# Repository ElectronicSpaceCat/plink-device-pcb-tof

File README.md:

# plink-device-pcb-tof
PCB for the Time of Flight (ToF) Sensors

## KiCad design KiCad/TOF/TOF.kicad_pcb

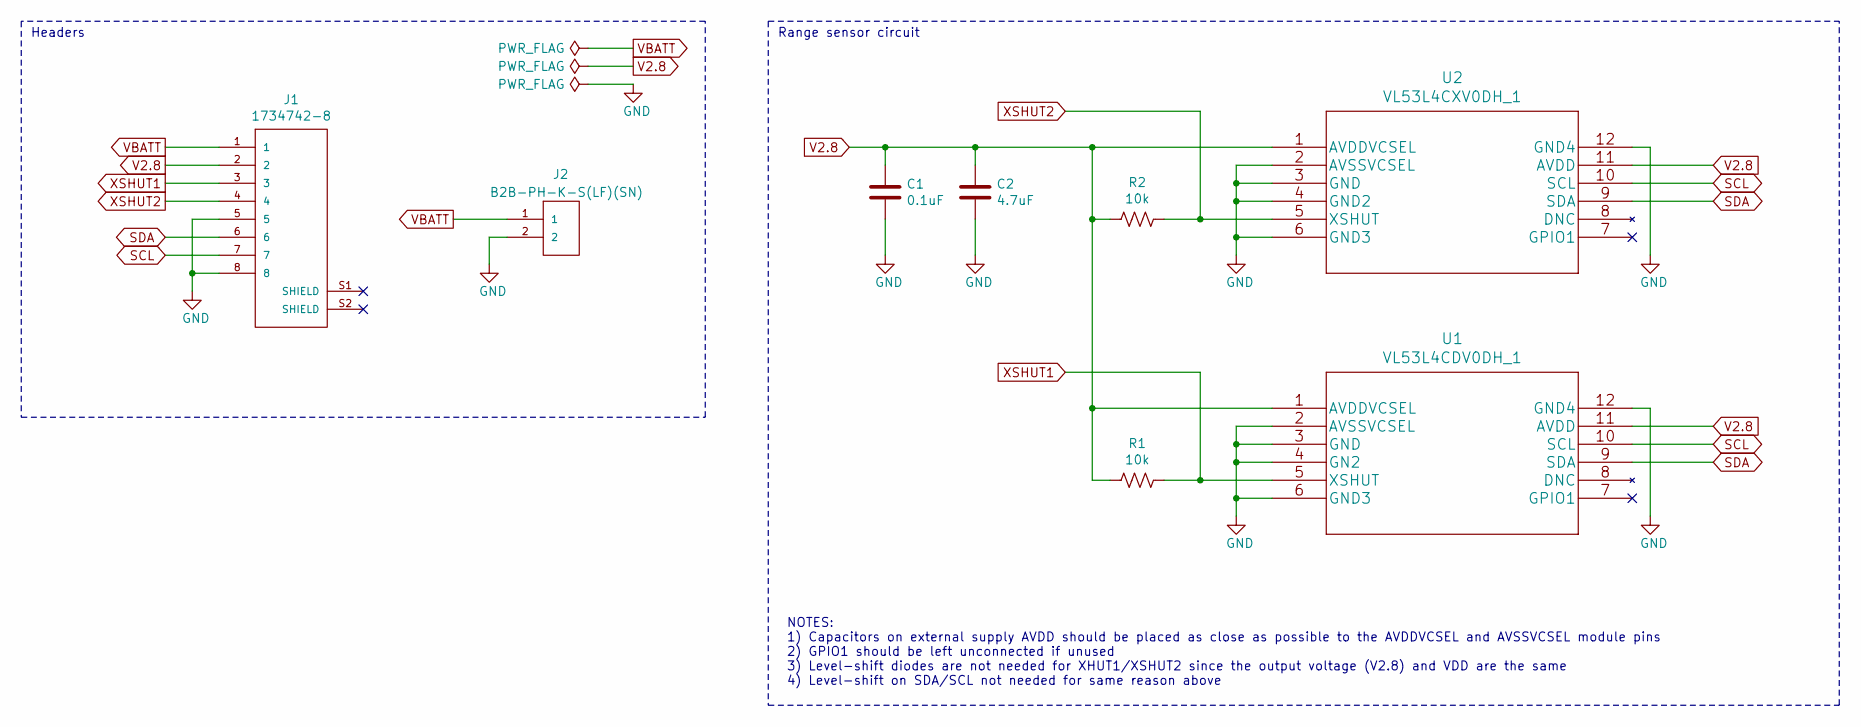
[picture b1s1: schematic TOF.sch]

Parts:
C1: 0.1uF; Capacitor_Taiyo_Yuden_0402
C2: 4.7uF; Capacitor_Taiyo_Yuden_0402
J1: 1734742-8; TE_1734742-8
J2: B2B-PH-K-S(LF)(SN); JST_B2B-PH-K-S(LF)(SN); PARTREV N/A; DIGI-KEY_PART_NUMBER 455-1704-ND
R1, R2: 10k; Stackpole_Res_0402
U1: VL53L4CDV0DH_1; VL53L4CDV0DH
U2: VL53L4CXV0DH_1; VL53L0CXV0DH&slash_1

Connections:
GND: C1.2, C2.2, J1.5, J1.8, J2.2, U1.2 (AVSSVCSEL), U1.3 (GND), U1.4 (GN2), U1.6 (GND3), U1.12 (GND4), U2.2 (AVSSVCSEL), U2.3 (GND), U2.4 (GND2), U2.6 (GND3), U2.12 (GND4)
SCL: J1.7, U1.10 (SCL), U2.10 (SCL)
SDA: J1.6, U1.9 (SDA), U2.9 (SDA)
V2.8: C1.1, C2.1, J1.2, R1.2, R2.2, U1.1 (AVDDVCSEL), U1.11 (AVDD), U2.1 (AVDDVCSEL), U2.11 (AVDD)
VBATT: J1.1, J2.1
XSHUT1: J1.3, R1.1, U1.5 (XSHUT)
XSHUT2: J1.4, R2.1, U2.5 (XSHUT)

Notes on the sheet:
Range sensor circuit
NOTES: 1) Capacitors on external supply AVDD should be placed as close as possible to the AVDDVCSEL and AVSSVCSEL module pins 2) GPIO1 should be left unconnected if unused 3) Level-shift diodes are not needed for XHUT1/XSHUT2 since the output voltage (V2.8) and VDD are the same 4) Level-shift on SD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
Headers

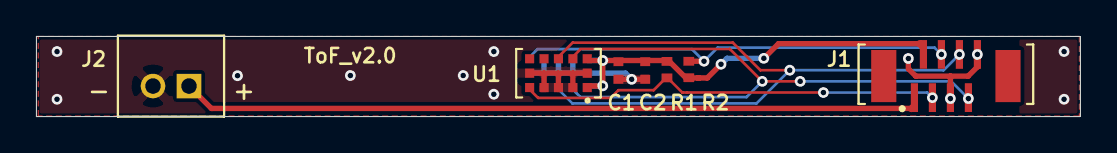
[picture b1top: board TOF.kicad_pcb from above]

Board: 2 copper layers, 58.0 x 4.5 mm, 8 parts (1 on the bottom side), 7 nets.

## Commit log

2023-02-25 Create LICENSE
